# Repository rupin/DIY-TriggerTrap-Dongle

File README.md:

DIY-TriggerTrap-Dongle
===========

An exceptional method of triggering DSLR cameras and upping your photography game

Included all necessary PCB files. If you dont intend to
modify the PCB, use the zip file, available on OSHPark (https://oshpark.com/shared_projects/3Ss2o3g2), 3.85 USD for a set of three. Share with friends the way I did!

Add the con-3.5mm-stereo-smt.lbr to eagle before proceeding to modify
the schematics and board.
BOM
2x 3.5mm stereo jacks
2x BC547 Through Hole NPN Transistor
2x 1.5k resistor
2x 3.5mm stereo cables

For Canon cameras, purchase a 3.5mm to 2.5mm stereo conversion jack. The conversion jack goes into the camera, and the 3.5mm cable connects into the conversion jack on one side and the PCB on the other (3.5mm jack on the board closest to the transistors)

Connect the phone with a 3.5mm stereo cable to the connector on the opposite side of the transistors. Download the triggertrap app and start using this amazing app+dongle to get some exceptional high speed shots of balloons blasting or cups smasing.

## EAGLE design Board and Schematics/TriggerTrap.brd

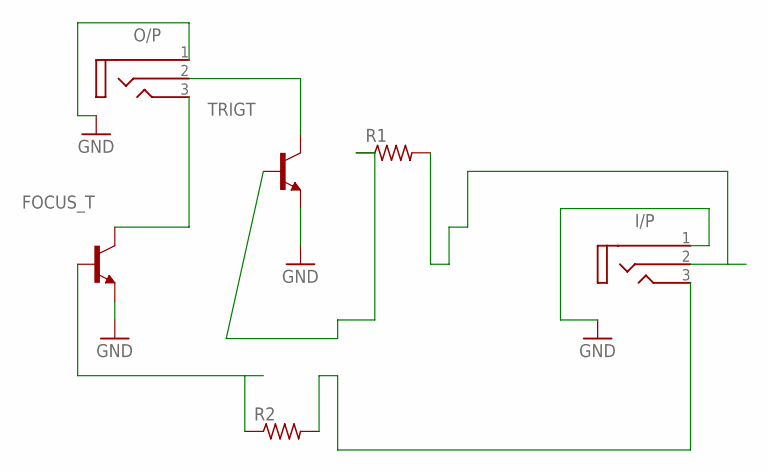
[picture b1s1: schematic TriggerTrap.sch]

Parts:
FOCUS_T: BC547; TO92
I/P: CON-3.5MM-STEREO-SMT
O/P: CON-3.5MM-STEREO-SMT
R1, R2: R-US_FLIPFLOP7; 0805-THM-7
TRIGT: BC547; TO92

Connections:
GND: FOCUS_T.1 (E), I/P.1, O/P.1, TRIGT.1 (E)
unnamed: FOCUS_T.2 (B), R2.1
unnamed: R1.1, TRIGT.2 (B)
unnamed: O/P.2, TRIGT.3 (C)
unnamed: FOCUS_T.3 (C), O/P.3
unnamed: I/P.3, R2.2
unnamed: I/P.2, R1.2

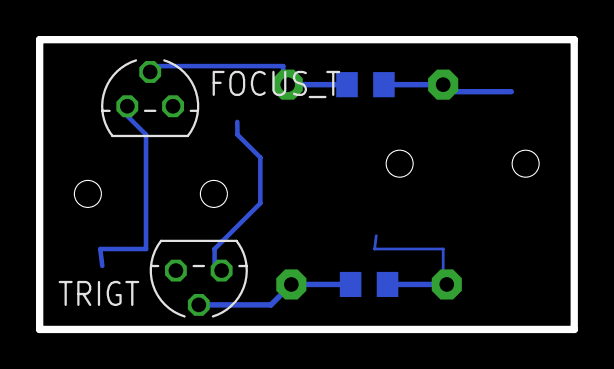
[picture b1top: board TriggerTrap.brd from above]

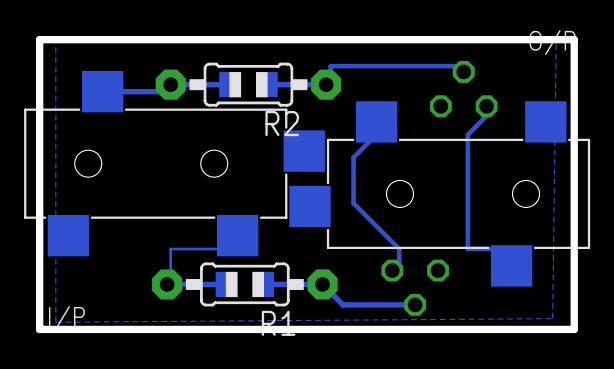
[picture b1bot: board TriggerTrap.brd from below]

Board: 2 copper layers, 29.7 x 16.1 mm, 6 parts (4 on the bottom side), 7 nets.

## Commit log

2014-09-05 Initial Commit
    Included all necessary PCB files with this commit. If you dont intend to
    modify the PCB, use the zip file.
    Add the con-3.5mm-stereo-smt.lbr to eagle before proceeding to modify
    the schematics and board.
    Available on OSHPark (https://oshpark.com/shared_projects/3Ss2o3g2) for
    3.85 USD for a set of three
2014-09-05 Cleanup
    Cleanup
